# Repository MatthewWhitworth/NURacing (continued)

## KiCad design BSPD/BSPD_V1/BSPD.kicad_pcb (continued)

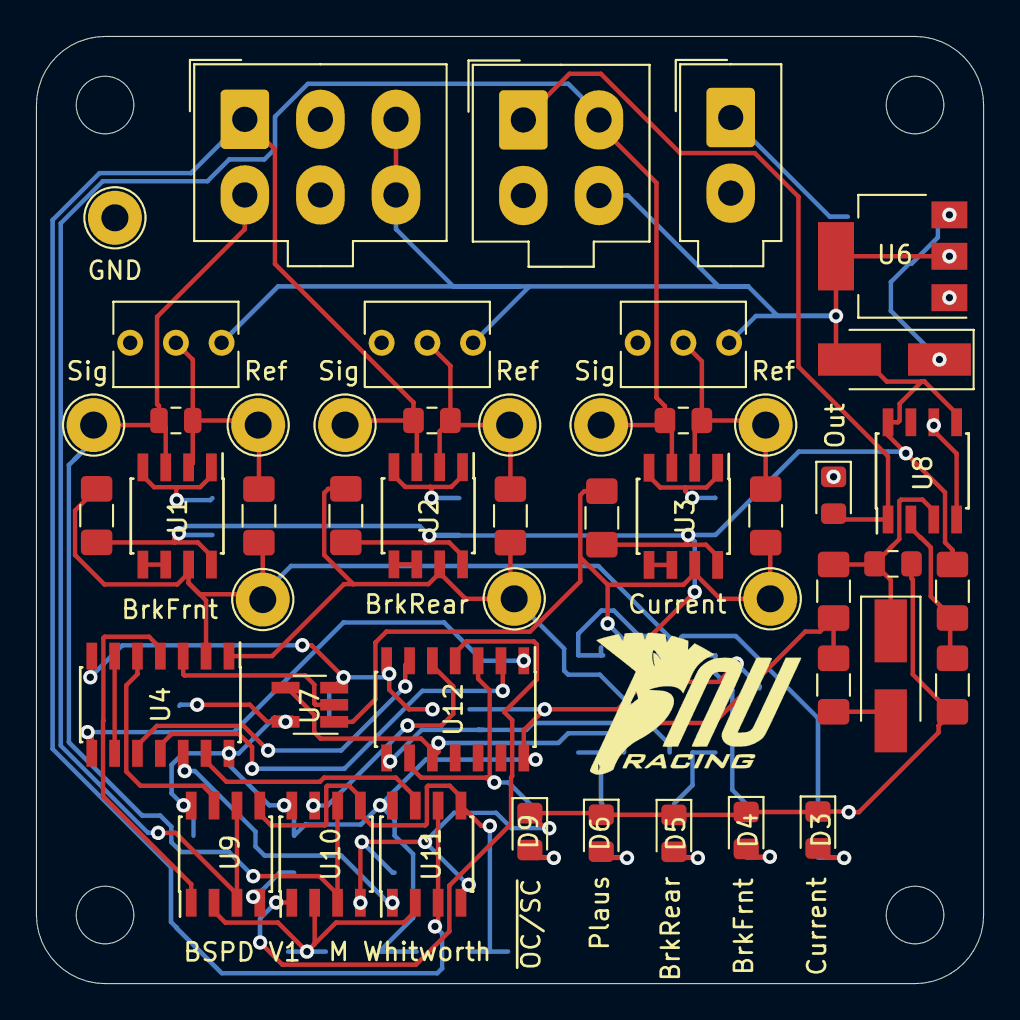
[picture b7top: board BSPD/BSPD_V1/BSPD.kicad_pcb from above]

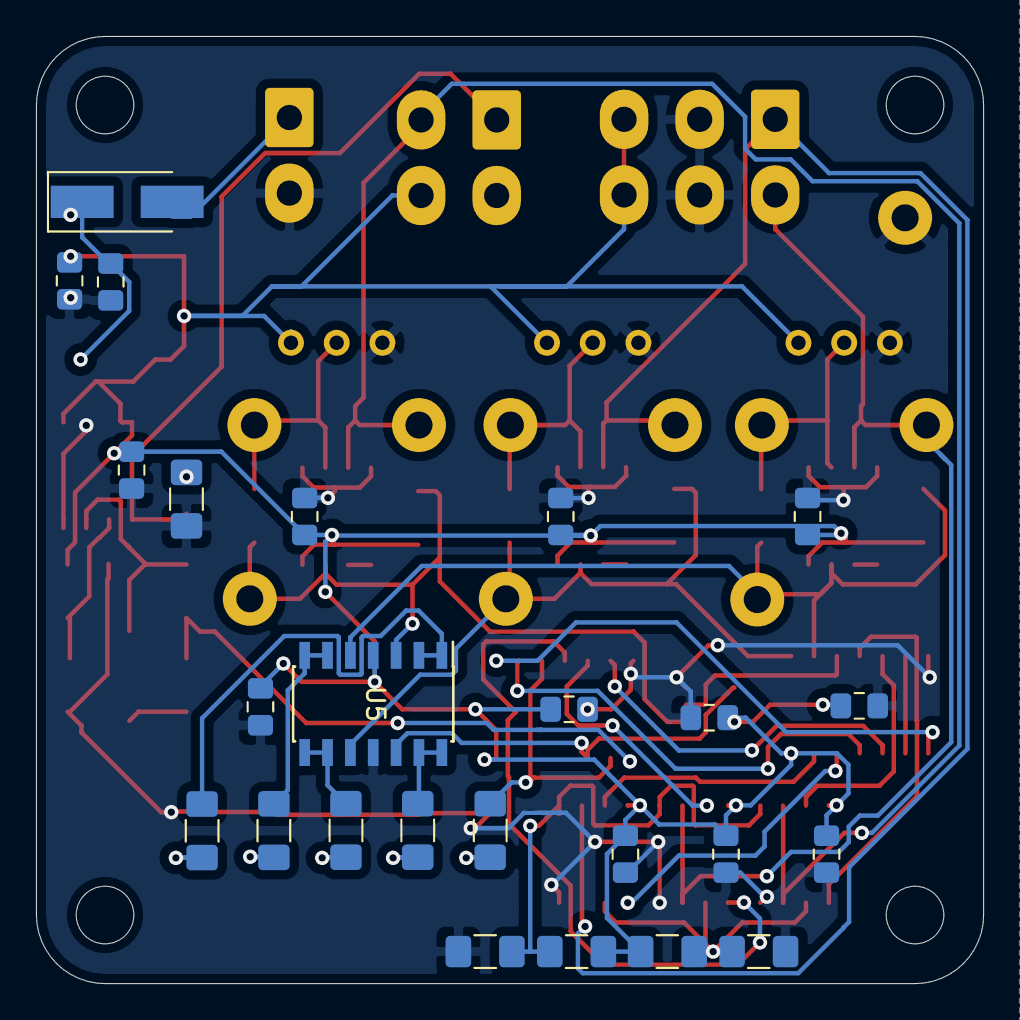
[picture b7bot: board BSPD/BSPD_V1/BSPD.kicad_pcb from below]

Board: 2 copper layers, 52.6 x 52.6 mm, 74 parts (25 on the bottom side), 46 nets.

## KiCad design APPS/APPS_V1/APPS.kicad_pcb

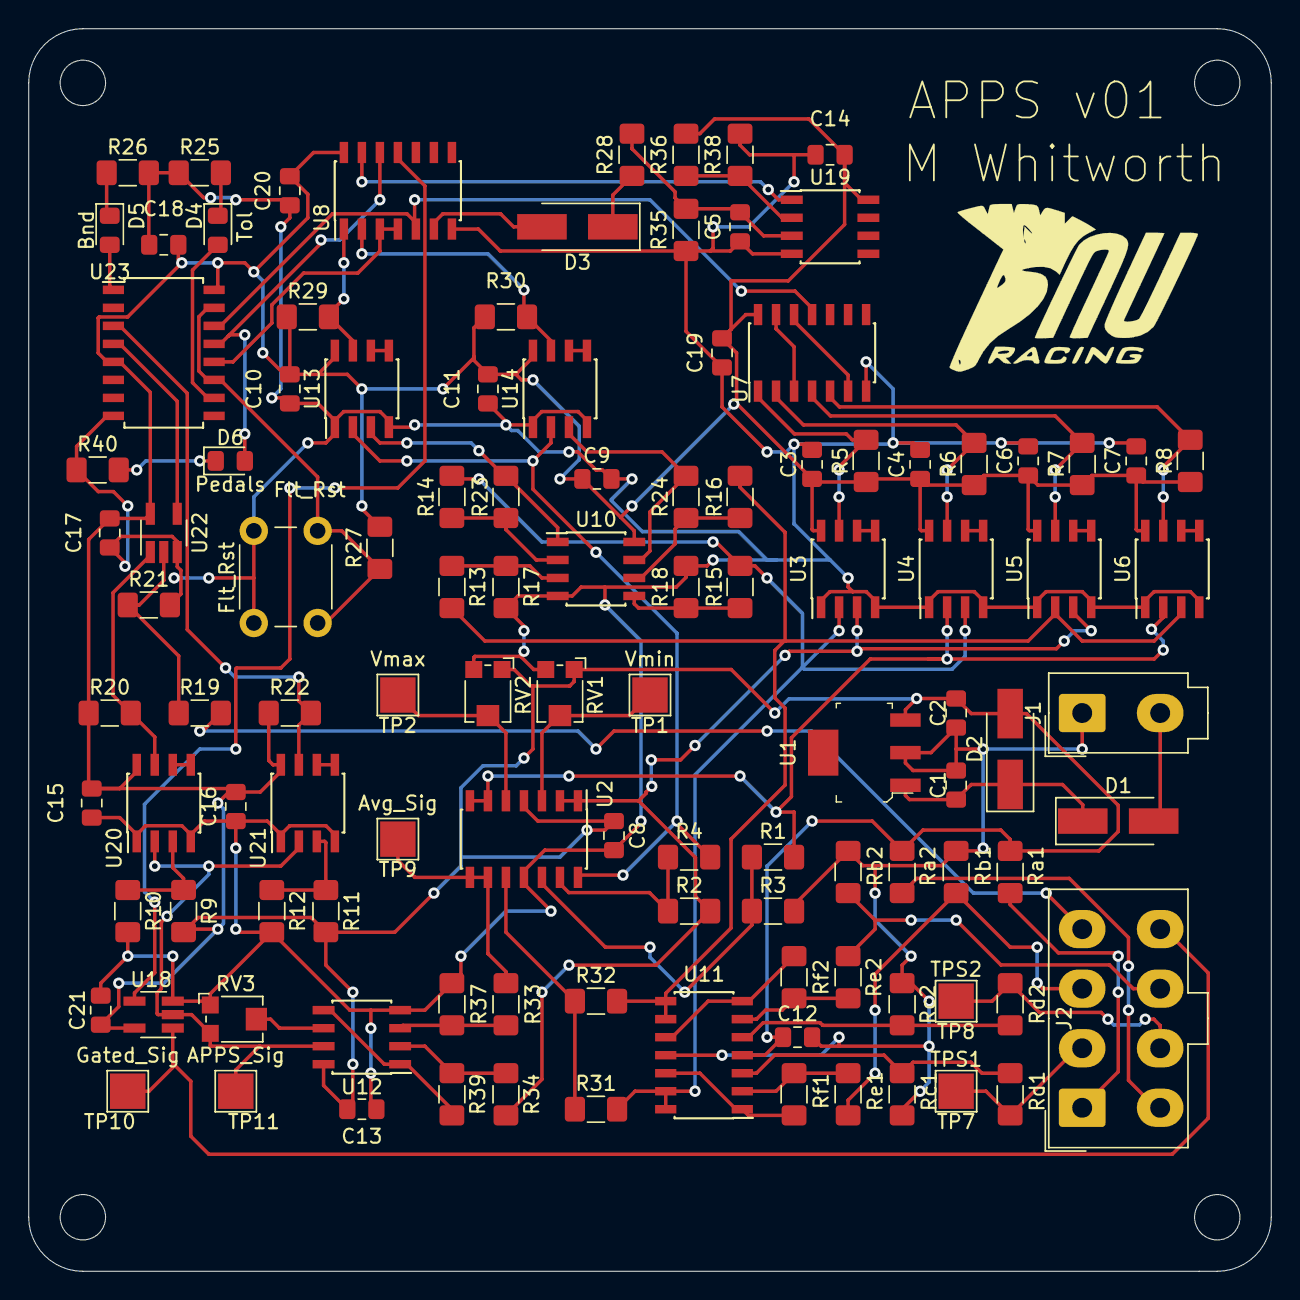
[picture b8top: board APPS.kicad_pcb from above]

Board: 2 copper layers, 87.6 x 87.6 mm, 111 parts (0 on the bottom side), 77 nets.

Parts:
C1: 0.33uF; C_0805_2012Metric_Pad1.15x1.40mm_HandSolder
C2, C3, C4, C6, C7, C8, C9, C10, C11, C12, C13, C14, C15, C16, C17, C18, C19, C20, C21: 0.1uF; C_0805_2012Metric_Pad1.15x1.40mm_HandSolder
C5: 2.2uF; C_0805_2012Metric_Pad1.15x1.40mm_HandSolder
D1, D2, D3: D; D_SMA_Handsoldering
D4: Tol; LED_0805_2012Metric_Pad1.15x1.40mm_HandSolder
D5: Bnd; LED_0805_2012Metric_Pad1.15x1.40mm_HandSolder
D6: Pedals; LED_0805_2012Metric_Pad1.15x1.40mm_HandSolder
J1: Conn_01x02_Female; Molex_Mini-Fit_Jr_5566-02A_2x01_P4.20mm_Vertical
J2: Conn_01x08_Female; Molex_Mini-Fit_Jr_5566-08A_2x04_P4.20mm_Vertical
R1, R2, R36: 100k; R_1206_3216Metric_Pad1.42x1.75mm_HandSolder
R3, R4, R5, R6, R7, R8, R13, R14, R15, R16, R17, R18, R20, R22, R23, R24, R27, R29, R30, R31, R32, R33, R34, R37, R38, R39: 10k; R_1206_3216Metric_Pad1.42x1.75mm_HandSolder
R9: 3k; R_1206_3216Metric_Pad1.42x1.75mm_HandSolder
R10: 1k; R_1206_3216Metric_Pad1.42x1.75mm_HandSolder
R11, R35: 20k; R_1206_3216Metric_Pad1.42x1.75mm_HandSolder
R12: 1.05k; R_1206_3216Metric_Pad1.42x1.75mm_HandSolder
R19: 6.8k; R_1206_3216Metric_Pad1.42x1.75mm_HandSolder
R21: 4.7k; R_1206_3216Metric_Pad1.42x1.75mm_HandSolder
R25, R26, R40: 470; R_1206_3216Metric_Pad1.42x1.75mm_HandSolder
R28: 2k; R_1206_3216Metric_Pad1.42x1.75mm_HandSolder
RV1, RV2, RV3: 10k; Potentiometer_Bourns_TC33X_Vertical
Ra1, Ra2: R; R_1206_3216Metric_Pad1.42x1.75mm_HandSolder
Rb1, Rb2: R; R_1206_3216Metric_Pad1.42x1.75mm_HandSolder
Rc1, Rc2: R; R_1206_3216Metric_Pad1.42x1.75mm_HandSolder
Rd1, Rd2: R; R_1206_3216Metric_Pad1.42x1.75mm_HandSolder
Re1, Re2: R; R_1206_3216Metric_Pad1.42x1.75mm_HandSolder
Rf1, Rf2: R; R_1206_3216Metric_Pad1.42x1.75mm_HandSolder
SW1: Flt_Rst; SW_PUSH_6mm
TP1: Vmin; TestPoint_Pad_2.5x2.5mm
TP2: Vmax; TestPoint_Pad_2.5x2.5mm
TP7: TPS1; TestPoint_Pad_2.5x2.5mm
TP8: TPS2; TestPoint_Pad_2.5x2.5mm
TP9: Avg_Sig; TestPoint_Pad_2.5x2.5mm
TP10: Gated_Sig; TestPoint_Pad_2.5x2.5mm
TP11: APPS_Sig; TestPoint_Pad_2.5x2.5mm
U1: L7805; SOT-223-4
U2, U11: MCP6004; SOIC-14_3.9x8.7mm_P1.27mm
U3, U4, U5, U6, U13, U14, U20, U21: LM311; SOIC-8_3.9x4.9mm_P1.27mm
U7, U8: AND_SN74HCT08; SOIC-14_3.9x8.7mm_P1.27mm
U10, U12, U19: MCP6002-xSN; SOIC-8_3.9x4.9mm_P1.27mm
U18: Analog_Switch; SOT-23-5_HandSoldering
U22: 74LVC1G00; SOT-23-5_HandSoldering
U23: CD4044B; SOIC-16W_5.3x10.2mm_P1.27mm

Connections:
12V: C1.1, D1.1, D2.1, U1.1
APPS_Output: J2.8, TP10.1, U18.1
APPS_Sig: RV3.3, TP11.1, U12.7, U18.2, U20.2, U21.2
Bnd_Flt: U7.11, U8.5, U23.14
Brake_Switch: J2.4, R19.2
Err_Rst: R27.1, SW1.2, U23.11, U23.15
Flt_Del: U8.13, U19.1
Flt_Sig: D3.2, U8.6
GND: C1.2, C2.2, C3.2, C4.2, C5.2, C6.2, C7.2, C8.2, C9.2, C10.2, C11.2, C12.2, C13.2, C14.2, C15.2, C16.2, C17.2, C18.2, C19.2, C20.2, C21.2, J1.1, R3.2, R10.2, R12.2, R17.2, R18.2, R21.2, R25.1, R26.2, R35.1, R37.2, R38.2, R40.1, RV1.3, RV2.3, RV3.1, Rb1.2, Rb2.2, Rc1.1, Rc2.1, SW1.1, U1.2, U2.11, U3.1, U3.4, U4.1, U4.4, U5.1, U5.4, U6.1, U6.4, U7.7, U8.7, U10.4, U11.11, U12.4, U13.1, U13.4, U14.1, U14.4, U18.3, U19.4, U20.1, U20.4, U21.1, U21.4, U22.3, U23.8
unnamed: C5.1, R28.1, R35.2, U19.3
unnamed: D1.2, J1.2
unnamed: D3.1, R28.2
unnamed: D4.1, R25.2
unnamed: D4.2, U23.10
unnamed: D5.1, R26.1
unnamed: D5.2, U23.1
unnamed: D6.1, R40.2
unnamed: R1.1, R3.1, U2.12
unnamed: R2.1, R4.1, U2.13
unnamed: R5.2, U3.7, U7.1
unnamed: R6.2, U4.7, U7.2
unnamed: R7.2, U5.7, U7.4
unnamed: R8.2, U6.7, U7.5
unnamed: R9.1, R10.1, U20.3
unnamed: R11.1, R12.1, U21.3
unnamed: R13.1, R17.1, U10.3
unnamed: R14.1, R23.1, U10.2
unnamed: R15.1, R18.1, U10.5
unnamed: R16.1, R24.1, U10.6
unnamed: R19.1, R21.1, U22.2
unnamed: R20.2, U20.7, U22.1
unnamed: R23.2, U10.1, U13.3
unnamed: R24.2, U10.7, U14.3
unnamed: R29.2, U8.1, U13.7
unnamed: R30.1, U8.2, U14.7
unnamed: R31.1, R32.1, U2.10
unnamed: R33.1, R37.1, U12.3
unnamed: R34.1, R39.1, U12.2
unnamed: R36.1, R38.1, U19.2
unnamed: R39.2, U12.1, U12.5
unnamed: RV1.2, TP1.1, U2.3
unnamed: RV2.2, TP2.1, U2.5
unnamed: RV3.2, U12.6
unnamed: Rc1.2, Rd1.1, U11.3
unnamed: Rc2.2, Rd2.1, U11.5
unnamed: Re1.2, Rf1.1, U11.2
unnamed: Re2.2, Rf2.1, U11.6
unnamed: Rf1.2, U11.1, U11.12
unnamed: Rf2.2, U11.7, U11.10
unnamed: U3.5, U3.6
unnamed: U4.5, U4.6
unnamed: U5.5, U5.6
unnamed: U6.5, U6.6
unnamed: U7.6, U7.12
unnamed: U7.3, U7.13
unnamed: U13.5, U13.6
unnamed: U14.5, U14.6
unnamed: U8.11, U18.4
unnamed: U20.5, U20.6
unnamed: U21.5, U21.6
Pdl_Flt: D6.2, U8.12, U23.13
Pdl_Rst: U22.4, U23.4
Pdl_Set: R22.2, U21.7, U23.3
Sig_Avg: R33.2, TP9.1, U2.8, U2.9
TPS_1: R14.2, R15.2, R31.2, U3.2, U4.3, U11.13, U11.14
TPS_1_In: J2.1, Ra1.2
TPS_1_Out: J2.3, Rb1.1, Re1.1
TPS_1_Sig: J2.2, Rd1.2, TP7.1
TPS_2: R13.2, R16.2, R32.2, U5.2, U6.3, U11.8, U11.9
TPS_2_In: J2.5, Ra2.2
TPS_2_Out: J2.7, Rb2.1, Re2.1
TPS_2_Sig: J2.6, Rd2.2, TP8.1
Tol_Flt: U8.3, U8.4, U23.12
Tolerance: R4.2, U2.14, U13.2, U14.2
VCC: C2.1, C3.1, C4.1, C6.1, C7.1, C8.1, C9.1, C10.1, C11.1, C12.1, C13.1, C14.1, C15.1, C16.1, C17.1, C18.1, C19.1, C20.1, C21.1, D2.2, R5.1, R6.1, R7.1, R8.1, R9.2, R11.2, R20.1, R22.1, R27.2, R29.1, R30.2, R36.2, RV1.1, RV2.1, Ra1.1, Ra2.1, U1.3, U2.4, U3.8, U4.8, U5.8, U6.8, U7.14, U8.14, U10.8, U11.4, U12.8, U13.8, U14.8, U18.5, U19.8, U20.8, U21.8, U22.5, U23.5, U23.16
Vmax: R1.2, U2.6, U2.7, U4.2, U6.2
Vmin: R2.2, R34.2, U2.1, U2.2, U3.3, U5.3

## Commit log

2021-01-31 First big commit
    uploading all current work on laptop
2021-02-01 Loom documentation/datasheets
    Loom documentation work and motec datasheets
2021-02-03 Loom documentation update
2021-02-04 BSPD and loom documentation
2021-02-08 BSPD acc board
2021-02-09 Updated loom schematic
2021-02-09 HPAcademy Documentation
2021-02-15 Updated topology connector documentation
2021-02-23 DR25 Datasheet
2021-03-09 Documentation updated
2021-03-09 Cooling Datalogger
    Datasheets and arduino sketches
2021-03-10 Documentation updates
2021-03-11 Cooling and loom documentation
2021-04-05 Overdue update
2021-04-19 CANbus code
2021-05-05 CAN pres
2021-05-06 CANBUS stuff
2021-05-06 Can pres finished
2021-05-11 Folder renames
2021-05-13 HFL system files
2021-05-14 Dash hard fault work
2021-05-16 Static prep names
2021-05-17 Dash work
2021-06-12 BSPD and enclosures
2021-07-08 Many Things
